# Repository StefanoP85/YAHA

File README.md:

# YAHA
YAHA: Yet Another Headphone Amplifier

This is my first electronic project, a simple headphone amplifier, clearly inspired by the TubeAmp from Dario Murgia's repository @ [https://github.com/Darmur/tubeamp]. I designed it, to fit in the same enclosure too.

| Reference | Quantity | Description | Mouser part number | RS part number | AliExpress |
| --------- | -------- | ----------- | ------------------ | -------------- | ---------- |
| R1, R102, R202|3|Resistore 4,7 KΩ 0,25 W|603-MFR-25FBF52-4K7|199-7625|
| R101, R201|2|Resistore 1 MΩ 0,125 W|603-MFR-12FTF52-1M|199-5032|
| R103, R203|2|Resistore 1 KΩ 0,25 W|603-MFR-25FBF52-1K|199-7601|
| R104, R204|2|Resistore 47 Ω 0,25 W|603-MFR-25FBF52-47R|199-7623|
| RV1|1|Potenziometro doppio audio 50 KΩ|688-RK09712200HA|249-9159|
| C1, C2|2|Condensatore elettrolitico 470 µF 16V|667-EEU-FC1C471B|249-1338|
| C3, C4|2|Condensatore ceramico multistrato 100nF 50V|594-K104K15X7RF5TH5|852-3277|
| C101, C201|2|Condensatore a film 2,2 µF 50V|80-R82CC4220Z370K |171-9233|
| C102, C202|2|Condensatore a film 1 nF 50V|594-K102K10X7RF53H5|240-4836|
| D1|1|LED rosso 3 mm|604-WP710A10SURC/E|619-4886|
| IC1|1|OPA2134PA|595-OPA2134PA|285-8069|
| IC2|1|TLE2426CLP|595-TLE2426CLPR||
| |1|Socket DIP-8|649-DILB8P223TLF|863-2734|
| |1|Connettore DC|710-694108301002|122-4883|https://www.aliexpress.com/item/33005175186.html
| |2|Jack audio 1/8" stereo 3P PJ-320A|||https://www.aliexpress.com/item/33029465106.html
| |1|Manopola per potenziometro|450-225||

Pictures of the components.

PCB back: the red one is the prototype, the black one is the current version.

PCB front: the red one is the prototype, the black one is the current version.

PCB assembled.

Amplifier completed, with the 3D printed enclosure.

The YAHA next to the TubeAmp from Dario Murgia.

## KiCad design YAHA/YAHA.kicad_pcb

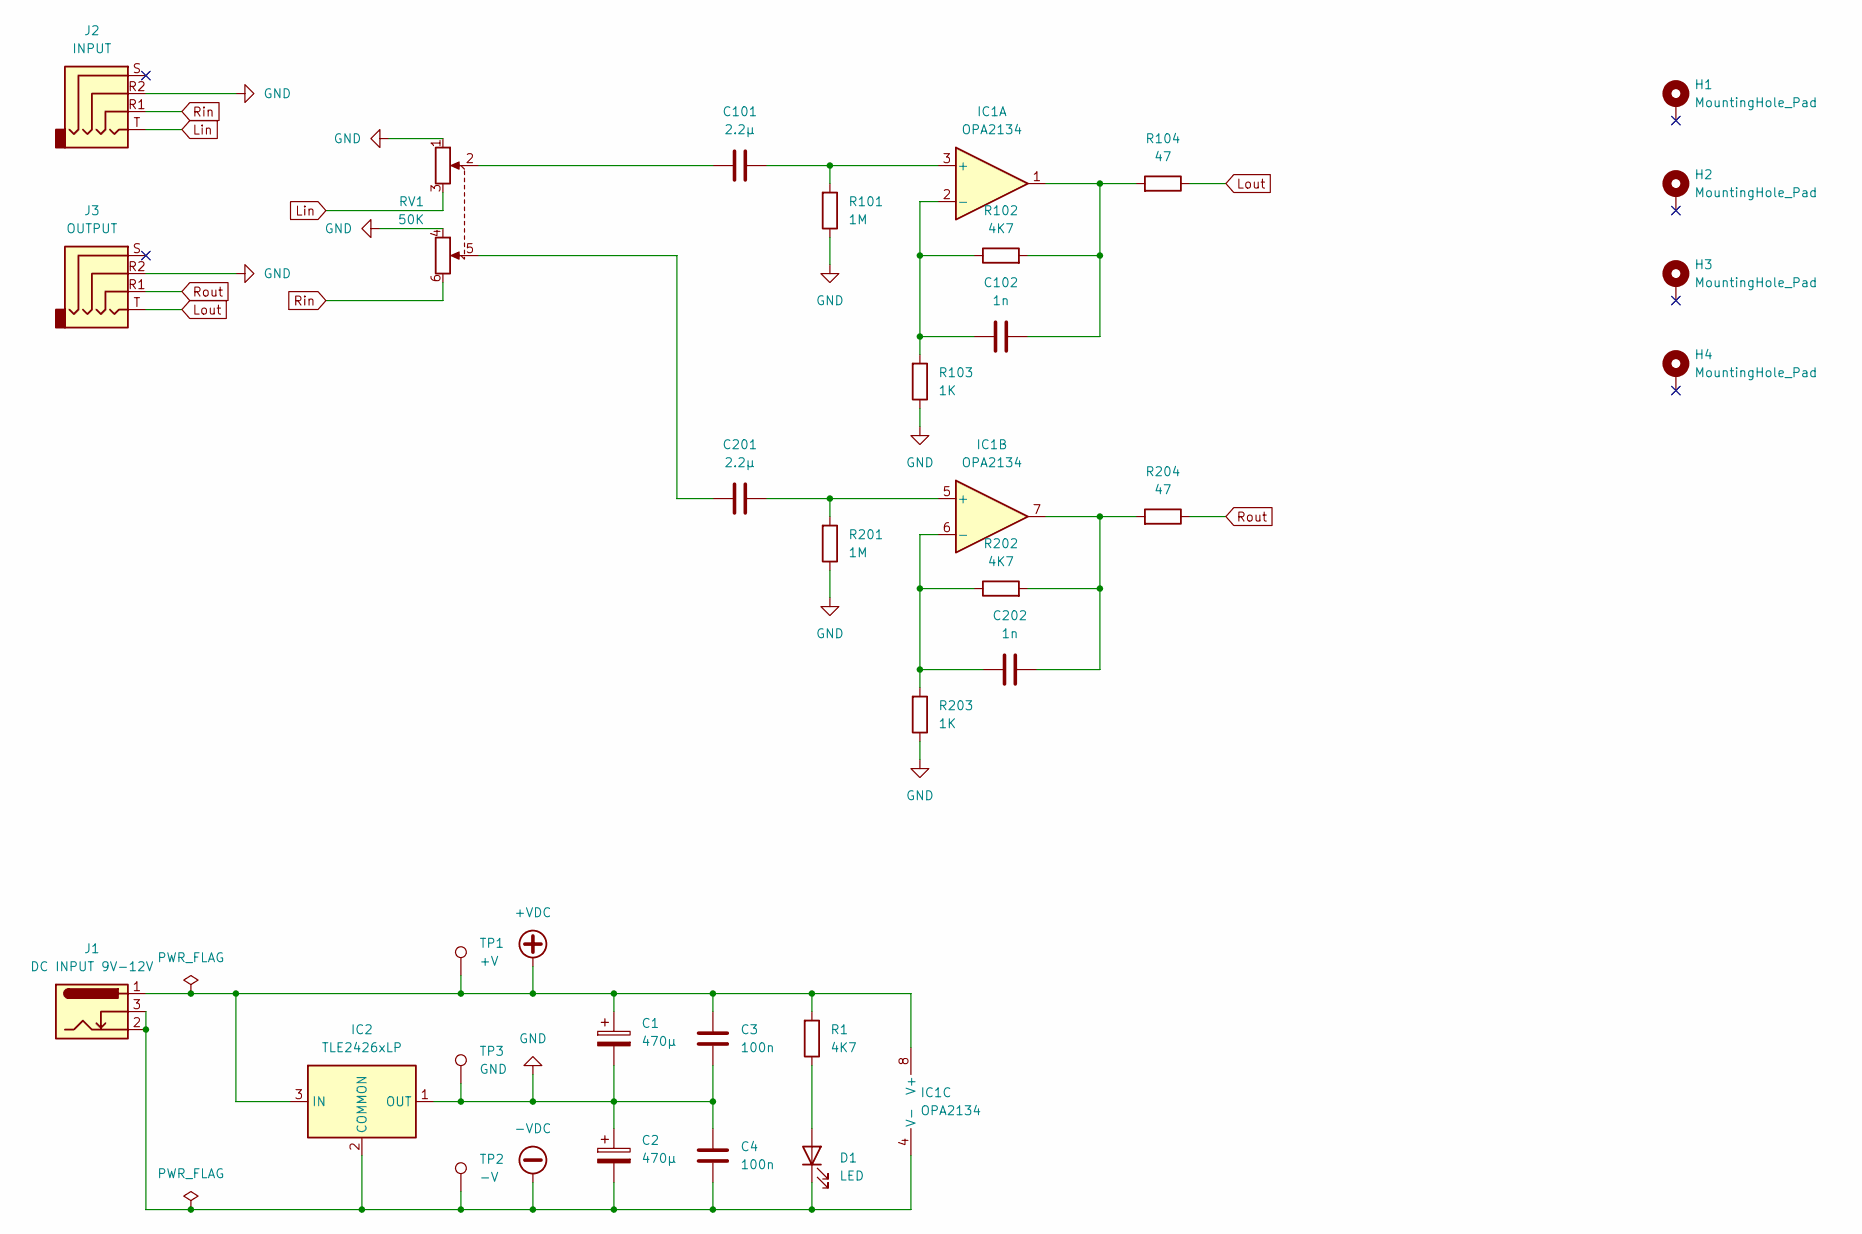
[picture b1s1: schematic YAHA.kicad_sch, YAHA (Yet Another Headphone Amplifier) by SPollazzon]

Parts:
C1, C2: 470µ; CP_Radial_D10.0mm_P5.00mm; Mouser part number 667-EEU-FC1C471B
C3, C4: 100n; C_Disc_D4.7mm_W2.5mm_P5.00mm; Mouser part number 594-K104K15X7RF5TH5
C101, C201: 2.2µ; C_Rect_L7.0mm_W6.0mm_P5.00mm; Mouser part number 80-R82CC4220Z370K
C102, C202: 1n; C_Disc_D4.7mm_W2.5mm_P5.00mm; Mouser part number 80-PFR5102J630J11L4
D1: LED; LED_D3.0mm; Mouser part number WP710A10SURC/E
H1, H2, H3, H4: MountingHole_Pad; MountingHole_2.5mm_Pad_Via
IC1: OPA2134; DIP-8_W7.62mm_Socket; Mouser part number 595-OPA2134PA, 649-DILB8P223TLF
IC2: TLE2426xLP; TO-92L_Inline_Wide; Mouser part number 595-TLE2426CLPR
J1: DC INPUT 9V-12V; BarrelJack_Horizontal
J2: INPUT; PJ-320A
J3: OUTPUT; PJ-320A
R1, R102, R202: 4K7; R_Axial_DIN0207_L6.3mm_D2.5mm_P7.62mm_Horizontal; Mouser part number 603-MFR-25FBF52-4K7
R101, R201: 1M; R_Axial_DIN0207_L6.3mm_D2.5mm_P7.62mm_Horizontal; Mouser part number 603-MFR-25FBF52-1M
R103, R203: 1K; R_Axial_DIN0207_L6.3mm_D2.5mm_P7.62mm_Horizontal; Mouser part number 603-MFR-25FBF52-1K
R104, R204: 47; R_Axial_DIN0207_L6.3mm_D2.5mm_P7.62mm_Horizontal; Mouser part number 603-MFR-25FBF52-47R
RV1: 50K; Potentiometer_Alps_RK097_Dual_Horizontal; Mouser part number 688-RK09712200HA
TP1: +V; TestPoint_Plated_Hole_D2.0mm
TP2: -V; TestPoint_Plated_Hole_D2.0mm
TP3: GND; TestPoint_Plated_Hole_D2.0mm

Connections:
+VDC: C1.1, C3.2, IC1.8 (V+), IC2.3 (IN), J1.1, R1.1, TP1.1
-VDC: C2.2, C4.1, D1.1 (K), IC1.4 (V-), IC2.2 (COMMON), J1.2, J1.3, TP2.1
GND: C1.2, C2.1, C3.1, C4.2, IC2.1 (OUT), J2.R2, J3.R2, R101.2, R103.2, R201.2, R203.2, RV1.1, RV1.4, TP3.1
Lin: J2.T, RV1.3
Lout: J3.T, R104.2
unnamed: C101.2, RV1.2
unnamed: C102.1, IC1.1, R102.1, R104.1
unnamed: C201.2, RV1.5
unnamed: C202.1, IC1.7, R202.1, R204.1
unnamed: D1.2 (A), R1.2
unnamed: C101.1, IC1.3 (+), R101.1
unnamed: C102.2, IC1.2 (-), R102.2, R103.1
unnamed: C201.1, IC1.5 (+), R201.1
unnamed: C202.2, IC1.6 (-), R202.2, R203.1
Rin: J2.R1, RV1.6
Rout: J3.R1, R204.2

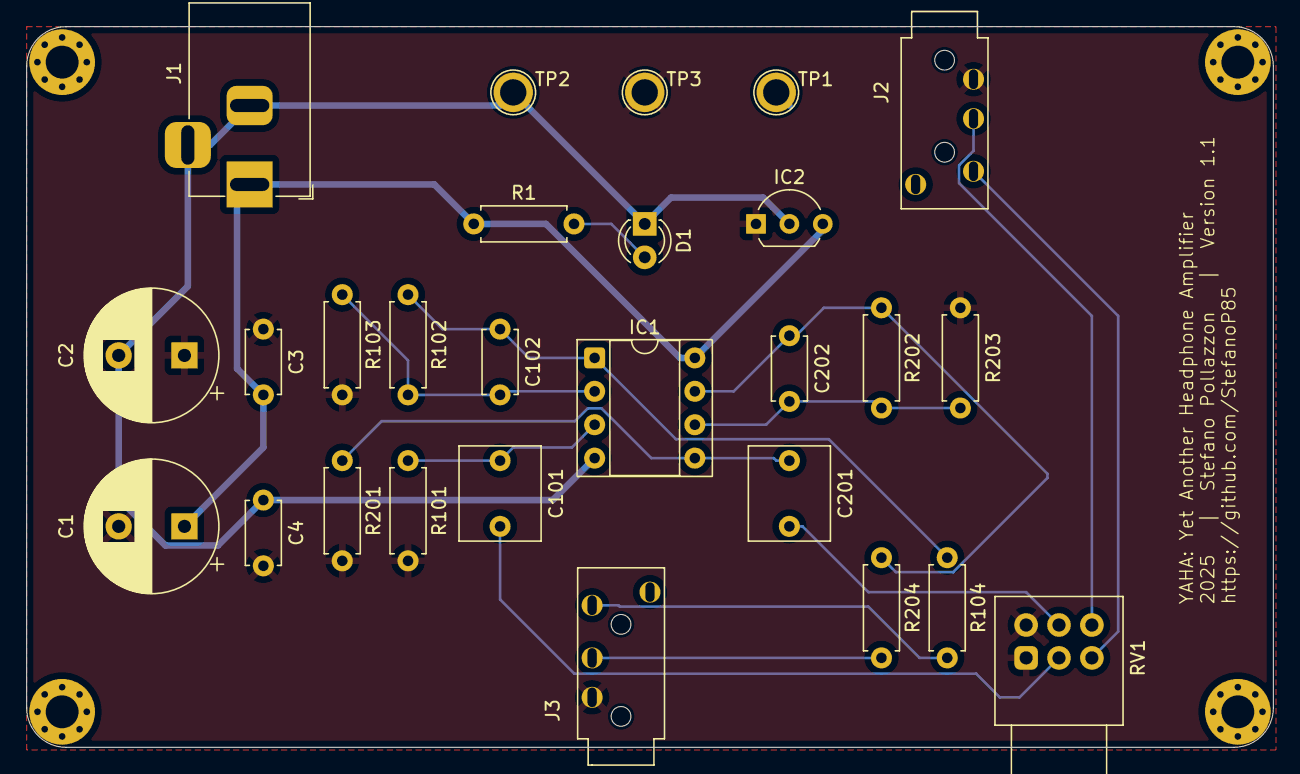
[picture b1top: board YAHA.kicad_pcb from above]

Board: 2 copper layers, 94.8 x 54.8 mm, 31 parts (0 on the bottom side), 16 nets.

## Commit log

2025-04-23 Add files via upload
    First version
2025-04-23 Rename 00 - Components.jpg to Media/00 - Components.jpg
    Move pictures in the media folder
2025-04-23 Rename 00 - PCB Front.jpg to Media/00 - PCB Front.jpg
    Move pictures in the media folder
2025-04-23 Rename 01 - Assembly.jpg to Media/01 - Assembly.jpg
    Move pictures in the media folder
2025-04-23 Rename 02 - Completed.jpg to Media/02 - Completed.jpg
    Move pictures in the media folder
2025-04-23 Rename 00 - PCB Back.jpg to Media/00 - PCB Back.jpg
    Move pictures in the media folder
2025-04-23 Rename Version 1.0.jpg to Media/Version 1.0.jpg
    Move pictures in the media folder
2025-04-23 Rename Version 1.1.png to Media/Version 1.1.png
    Move pictures in the media folder
2025-04-23 Delete Media/00 - Components.jpg
    Move pictures in the media folder
2025-04-23 Delete Media/00 - PCB Front.jpg
    Move pictures in the media folder
2025-04-23 Delete Media/01 - Assembly.jpg
    Move pictures in the media folder
2025-04-23 Delete Media/02 - Completed.jpg
    Move pictures in the media folder
2025-04-23 Add files via upload
    Move pictures in the media folder
